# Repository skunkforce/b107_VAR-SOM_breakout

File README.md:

# edgy_board number b107
This design is part of the [edgy board project](https://github.com/skunkforce/edgy_boards).

# getting started
This repository uses submodules. After cloning use the command 

```$ git submodule update --init --recursive```

to pull the submodules before opening the project with kicad. 

# Tests
Tests can be found in [TESTS.md](TESTS.md)

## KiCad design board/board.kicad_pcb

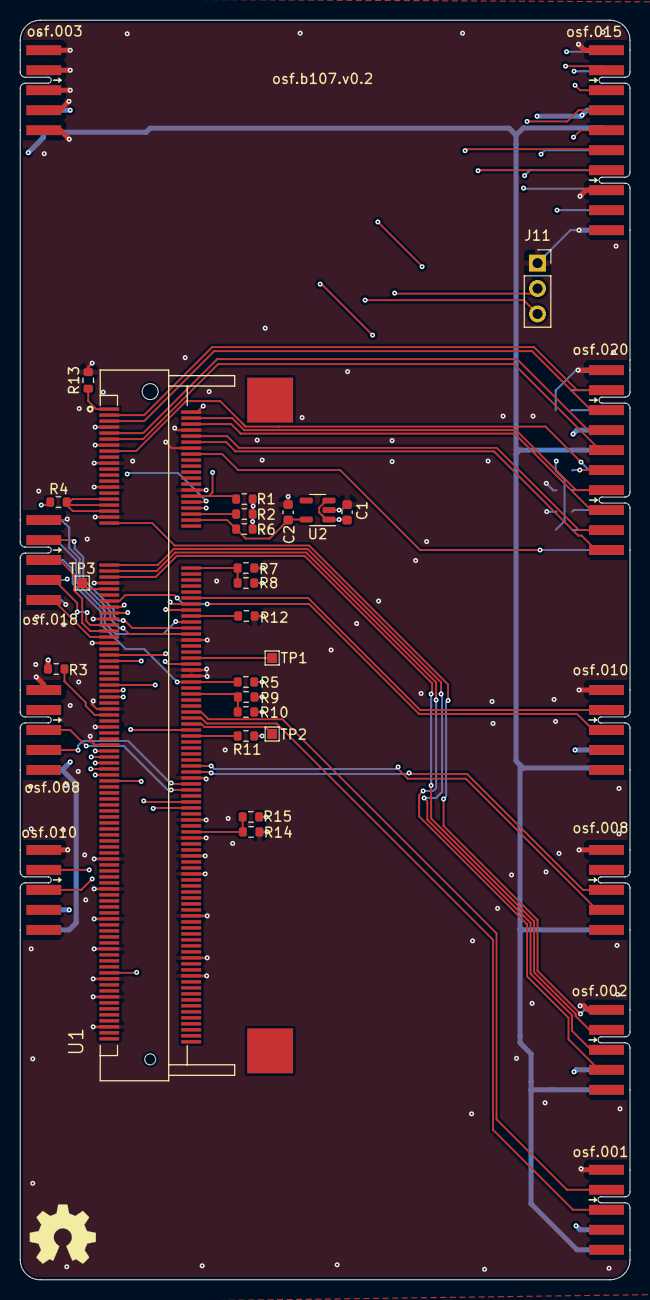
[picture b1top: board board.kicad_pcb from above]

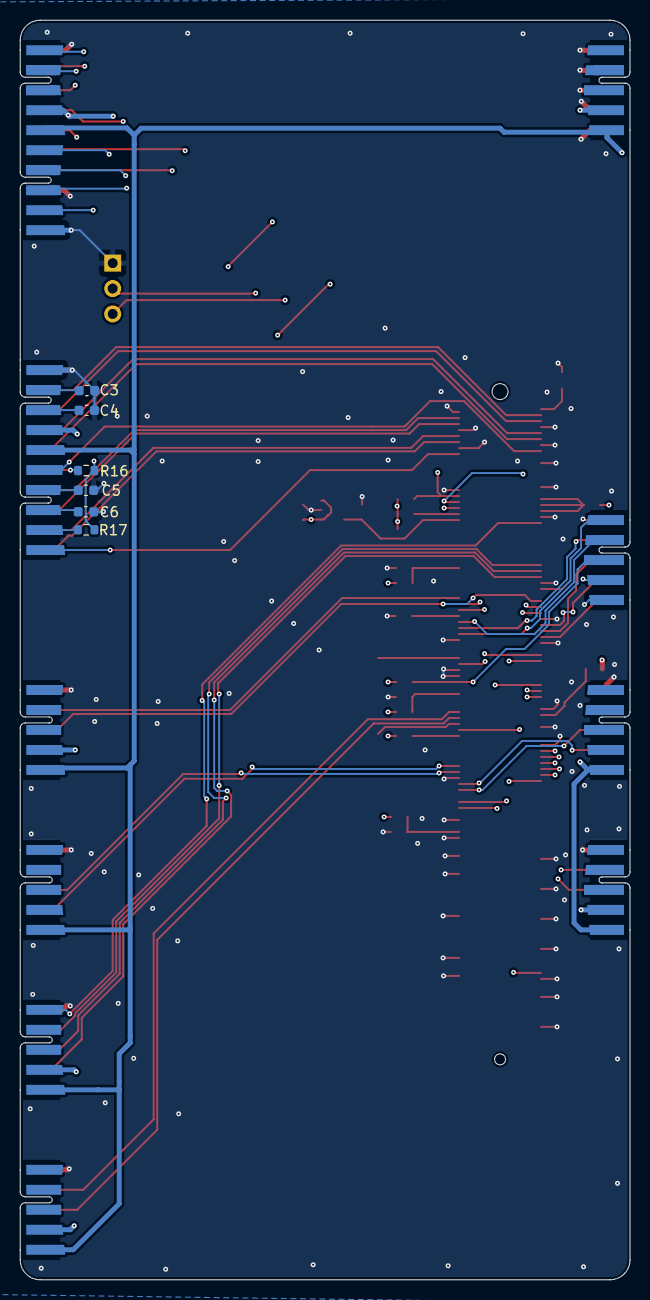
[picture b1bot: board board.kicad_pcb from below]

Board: 4 copper layers, 61.0 x 126.0 mm, 40 parts (6 on the bottom side), 67 nets.

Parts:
C1, C2: 4.7uF; C_0603_1608Metric
C3, C4, C5, C6: 100nF; C_0603_1608Metric
J1: 020_1000BASE-T_with_CT; on_edge_2x10_host
J2: 003_power; on_edge_2x05_device
J3: 008_USB; on_edge_2x05_device
J4: 001_I2C; on_edge_2x05_host
J5: 008_USB; on_edge_2x05_host
J6: 002_SPI; on_edge_2x05_host
J7: 010_UART; on_edge_2x05_host
J8: 015_RGMII; on_edge_2x10_host
J9: 010_UART; on_edge_2x05_device
J10: 018_QSPI; on_edge_2x05_device
J11: Conn_01x03_Male; PinSocket_1x03_P2.54mm_Vertical
LOGO1: Logo_Open_Hardware_Small; OSHW-Symbol_6.7x6mm_SilkScreen
R1, R2, R6, R9, R12, R13, R14: 0R; R_0603_1608Metric
R3, R7, R8, R10, R11, R15: 560R; R_0603_1608Metric
R4: d.n.p; R_0603_1608Metric
R5: 10k; R_0603_1608Metric
R16, R17: 49.9R; R_0603_1608Metric
TP1: USB_B_VBUS_ID1; TestPoint_Pad_1.0x1.0mm
TP2: USB_B_VBUS_ID2; TestPoint_Pad_1.0x1.0mm
TP3: base_peripherals_power; TestPoint_Pad_1.0x1.0mm
U1: VAR-SOM; TE_1473149-4
U2: TLV71318PQDBVRQ1; SOT-23-5

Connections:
+3.3V: C1.1, J1.14 (3.3V), J2.9 (3.3V), J4.9 (3.3V), J6.9 (3.3V), J7.9 (3.3V), J8.14 (3.3V), J9.9 (3.3V), J10.9 (3.3V), R1.1, R2.1, R3.2, R4.2, R5.2, R6.1, R8.2, R10.2, R11.2, R15.2, R16.1, R17.1, U1.32 (VCC_3V3_IN), U1.34 (VCC_3V3_IN), U1.103 (VCC_3V3_IN), U1.105 (VCC_3V3_IN), U1.107 (VCC_3V3_IN), U1.109 (VCC_3V3_IN), U1.111 (VCC_3V3_IN), U2.1 (IN), U2.3 (EN)
+5V: J1.15 (5V), J2.10 (5V), J3.10 (5V), J4.10 (5V), J5.10 (5V), J6.10 (5V), J7.10 (5V), J8.15 (5V), J9.10 (5V)
/UART5_RX: J7.3 (RX), U1.53 (BT_UART_RX)
/UART5_TX: J7.2 (TX), U1.52 (BT_UART_TX)
/led1: J1.16 (LED1_2), U1.15 (LINKSPEED)
/led2: J1.20 (LED2_2), U1.16 (LINKLED)
/var-som/DEBUG_UART_RX: J9.2 (TX), U1.83 (DEBUG_UART_RX)
/var-som/DEBUG_UART_TX: J9.3 (RX), U1.85 (DEBUG_UART_TX)
/var-som/ENET1_RXC: J8.11 (RXC), U1.57 (UART5_RTS)
/var-som/ENET1_RXD0: J8.16 (RXD0), U1.122 (GPIO5_9)
/var-som/ENET1_RXD1: J8.17 (RXD1), U1.81 (GPIO5_7)
/var-som/ENET1_RXD2: J8.18 (RXD2), U1.71 (NAND_CE1_B)
/var-som/ENET1_RXD3: J8.19 (RXD3), U1.54 (UART5_RX)
/var-som/ENET1_RX_CTL: J8.12 (RX_CTL), U1.120 (GPIO5_5)
/var-som/ENET1_TXC: J8.2 (TXC), U1.96 (LCD_DATA6)
/var-som/ENET1_TXD0: J8.3 (TXD0), U1.73 (GPIO5_1)
/var-som/ENET1_TXD1: J8.4 (TXD1), U1.177 (GPIO5_8)
/var-som/ENET1_TXD2: J8.5 (TXD2), U1.56 (UART5_TX)
/var-som/ENET1_TXD3: J8.6 (TXD3), U1.55 (UART5_CTS)
/var-som/ENET1_TX_CTL: J8.7 (TX_CTL), U1.113 (LCD_DATA7)
/var-som/ETH1_VDDIO: C2.1, R6.2, U1.38 (VCC_3V3_IN), U2.5 (OUT)
/var-som/ETH_A_MDI_A+: J1.2 (TD1+), U1.3 (ETH_RXDP)
/var-som/ETH_A_MDI_A-: J1.3 (TD1-), U1.5 (ETH_RXDN)
/var-som/ETH_A_MDI_B+: J1.4 (TD2+), U1.9 (ETH_TXDP)
/var-som/ETH_A_MDI_B-: J1.5 (TD2-), U1.11 (ETH_TXDN)
/var-som/ETH_A_MDI_C+: J1.7 (TD3+), U1.4
/var-som/ETH_A_MDI_C-: J1.8 (TD3-), U1.6
/var-som/ETH_A_MDI_D+: J1.9 (TD4+), U1.10
/var-som/ETH_A_MDI_D-: J1.10 (TD4-), U1.12
/var-som/I2C3_SCL: J4.3 (SCL), U1.92 (I2C3_SCL)
/var-som/I2C3_SDA: J4.2 (SDA), U1.90 (I2C3_SDA)
/var-som/MDC: J11.3, U1.74 (MDC)
/var-som/MDIO: J11.2, R1.2, U1.30 (MDIO)
/var-som/SPI4_MISO: J6.3 (MISO), U1.41 (ECSPI4_MISO)
/var-som/SPI4_MOSI: J6.2 (MOSI), U1.45 (ECSPI4_MOSI)
/var-som/SPI4_SCLK: J6.4 (SCLK), U1.43 (ECSPI4_SCLK)
/var-som/SPI4_SS: J6.6 (CS), U1.39 (ECSPI4_SS0)
/var-som/USB_A_D+: J5.3 (DP), U1.110 (USB_OTG2_DP)
/var-som/USB_A_D-: J5.4 (DM), U1.108 (USB_OTG2_DN)
/var-som/USB_B_D+: J3.3 (DP), U1.116 (USB_OTG1_DP)
/var-som/USB_B_D-: J3.4 (DM), U1.114 (USB_OTG1_DN)
/var-som/USB_B_VBUS_ID1: TP1.1, U1.72 (GPIO5_3)
/var-som/USB_B_VBUS_ID2: TP2.1, U1.94 (OTG1_ID)
/var-som/bootsel_a: R7.2, R8.1, U1.42 (BOOT_SEL)
/var-som/bootsel_b: J10.8 (SW0), R5.1, U1.80 (GPIO1_0)
/var-som/somtimes_power: R4.1, U1.31 (DGND), U1.33 (DGND), U1.35 (DGND)
/var-som/uSDHC_CLK: J10.7 (SCLK), U1.60 (CONN_CLK)
/var-som/uSDHC_CMD: J10.6 (CS), U1.64 (CONN_CMD)
/var-som/uSDHC_D0: J10.2 (SD0), U1.62 (CONN_DATA0)
/var-som/uSDHC_D1: J10.3 (SD1), U1.63 (CONN_DATA1)
/var-som/uSDHC_D2: J10.4 (SD2), U1.61 (CONN_DATA2)
/var-som/uSDHC_D3: J10.5 (SD3), U1.65 (CONN_DATA3)
GND: C1.2, C2.2, C3.2, C4.2, C5.2, C6.2, J1.1 (GND), J1.11 (GND), J2.1 (GND), J2.2 (GND), J2.3 (GND), J2.4 (GND), J2.5 (GND), J3.1 (GND), J4.1 (GND), J5.1 (GND), J6.1 (GND), J7.1 (GND), J8.1 (GND), J8.8 (GND), J8.20 (GND), J9.1 (GND), J10.1 (GND), J10.10 (SW1), J11.1, R7.1, R9.1, R12.1, R13.2, R14.1, U1.2 (DGND), U1.7 (DGND), U1.8 (DGND), U1.13 (DNGD), U1.14 (DGND), U1.19 (DGND), U1.27 (DGND), U1.28 (DGND), U1.37 (DGND), U1.47 (DGND), U1.59 (DGND), U1.66 (DGND), U1.67 (DGND), U1.76 (DGND), U1.78 (DGND), U1.89 (DGND), U1.95 (DGND), U1.101 (DGND), U1.112 (DGND), U1.126 (DGND), U1.132 (DGND), U1.138 (DGND), U1.139 (DGND), U1.144 (DGND), U1.149 (DGND), U1.158 (DGND), U1.159 (DGND), U1.169 (DGND), U1.172 (DGND), U1.178 (DGND), U1.179 (DGND), U1.185 (DGND), U1.195 (AGND), U2.2 (GND)
unnamed: J1.6 (LED1_1), R16.2
unnamed: C3.1, J1.12 (CT1)
unnamed: C4.1, J1.13 (CT2)
unnamed: C5.1, J1.17 (CT3)
unnamed: C6.1, J1.18 (CT4)
unnamed: J1.19 (LED2_1), R17.2
unnamed: R2.2, U1.36 (VCC_COIN)
unnamed: R3.1, U1.91 (BOOT1)
unnamed: R9.2, R10.1, U1.84 (DEBUG_UART_RTS_B)
unnamed: R11.1, U1.98 (POR)
unnamed: R12.2, U1.58 (DGND)
unnamed: R13.1, U1.1 (DGND)
unnamed: R14.2, R15.1, U1.130 (USB_OTG1_CHD_B)
unnamed: TP3.1, U1.49 (VCC_3V3)

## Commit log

2023-03-06 initial
2023-03-07 added RGMII interface
2023-03-07 added uSD card
2023-03-09 added 1.8v power option for RGMII IO
2023-03-19 increased spacing
2023-05-15 Update PU/PDn and values
